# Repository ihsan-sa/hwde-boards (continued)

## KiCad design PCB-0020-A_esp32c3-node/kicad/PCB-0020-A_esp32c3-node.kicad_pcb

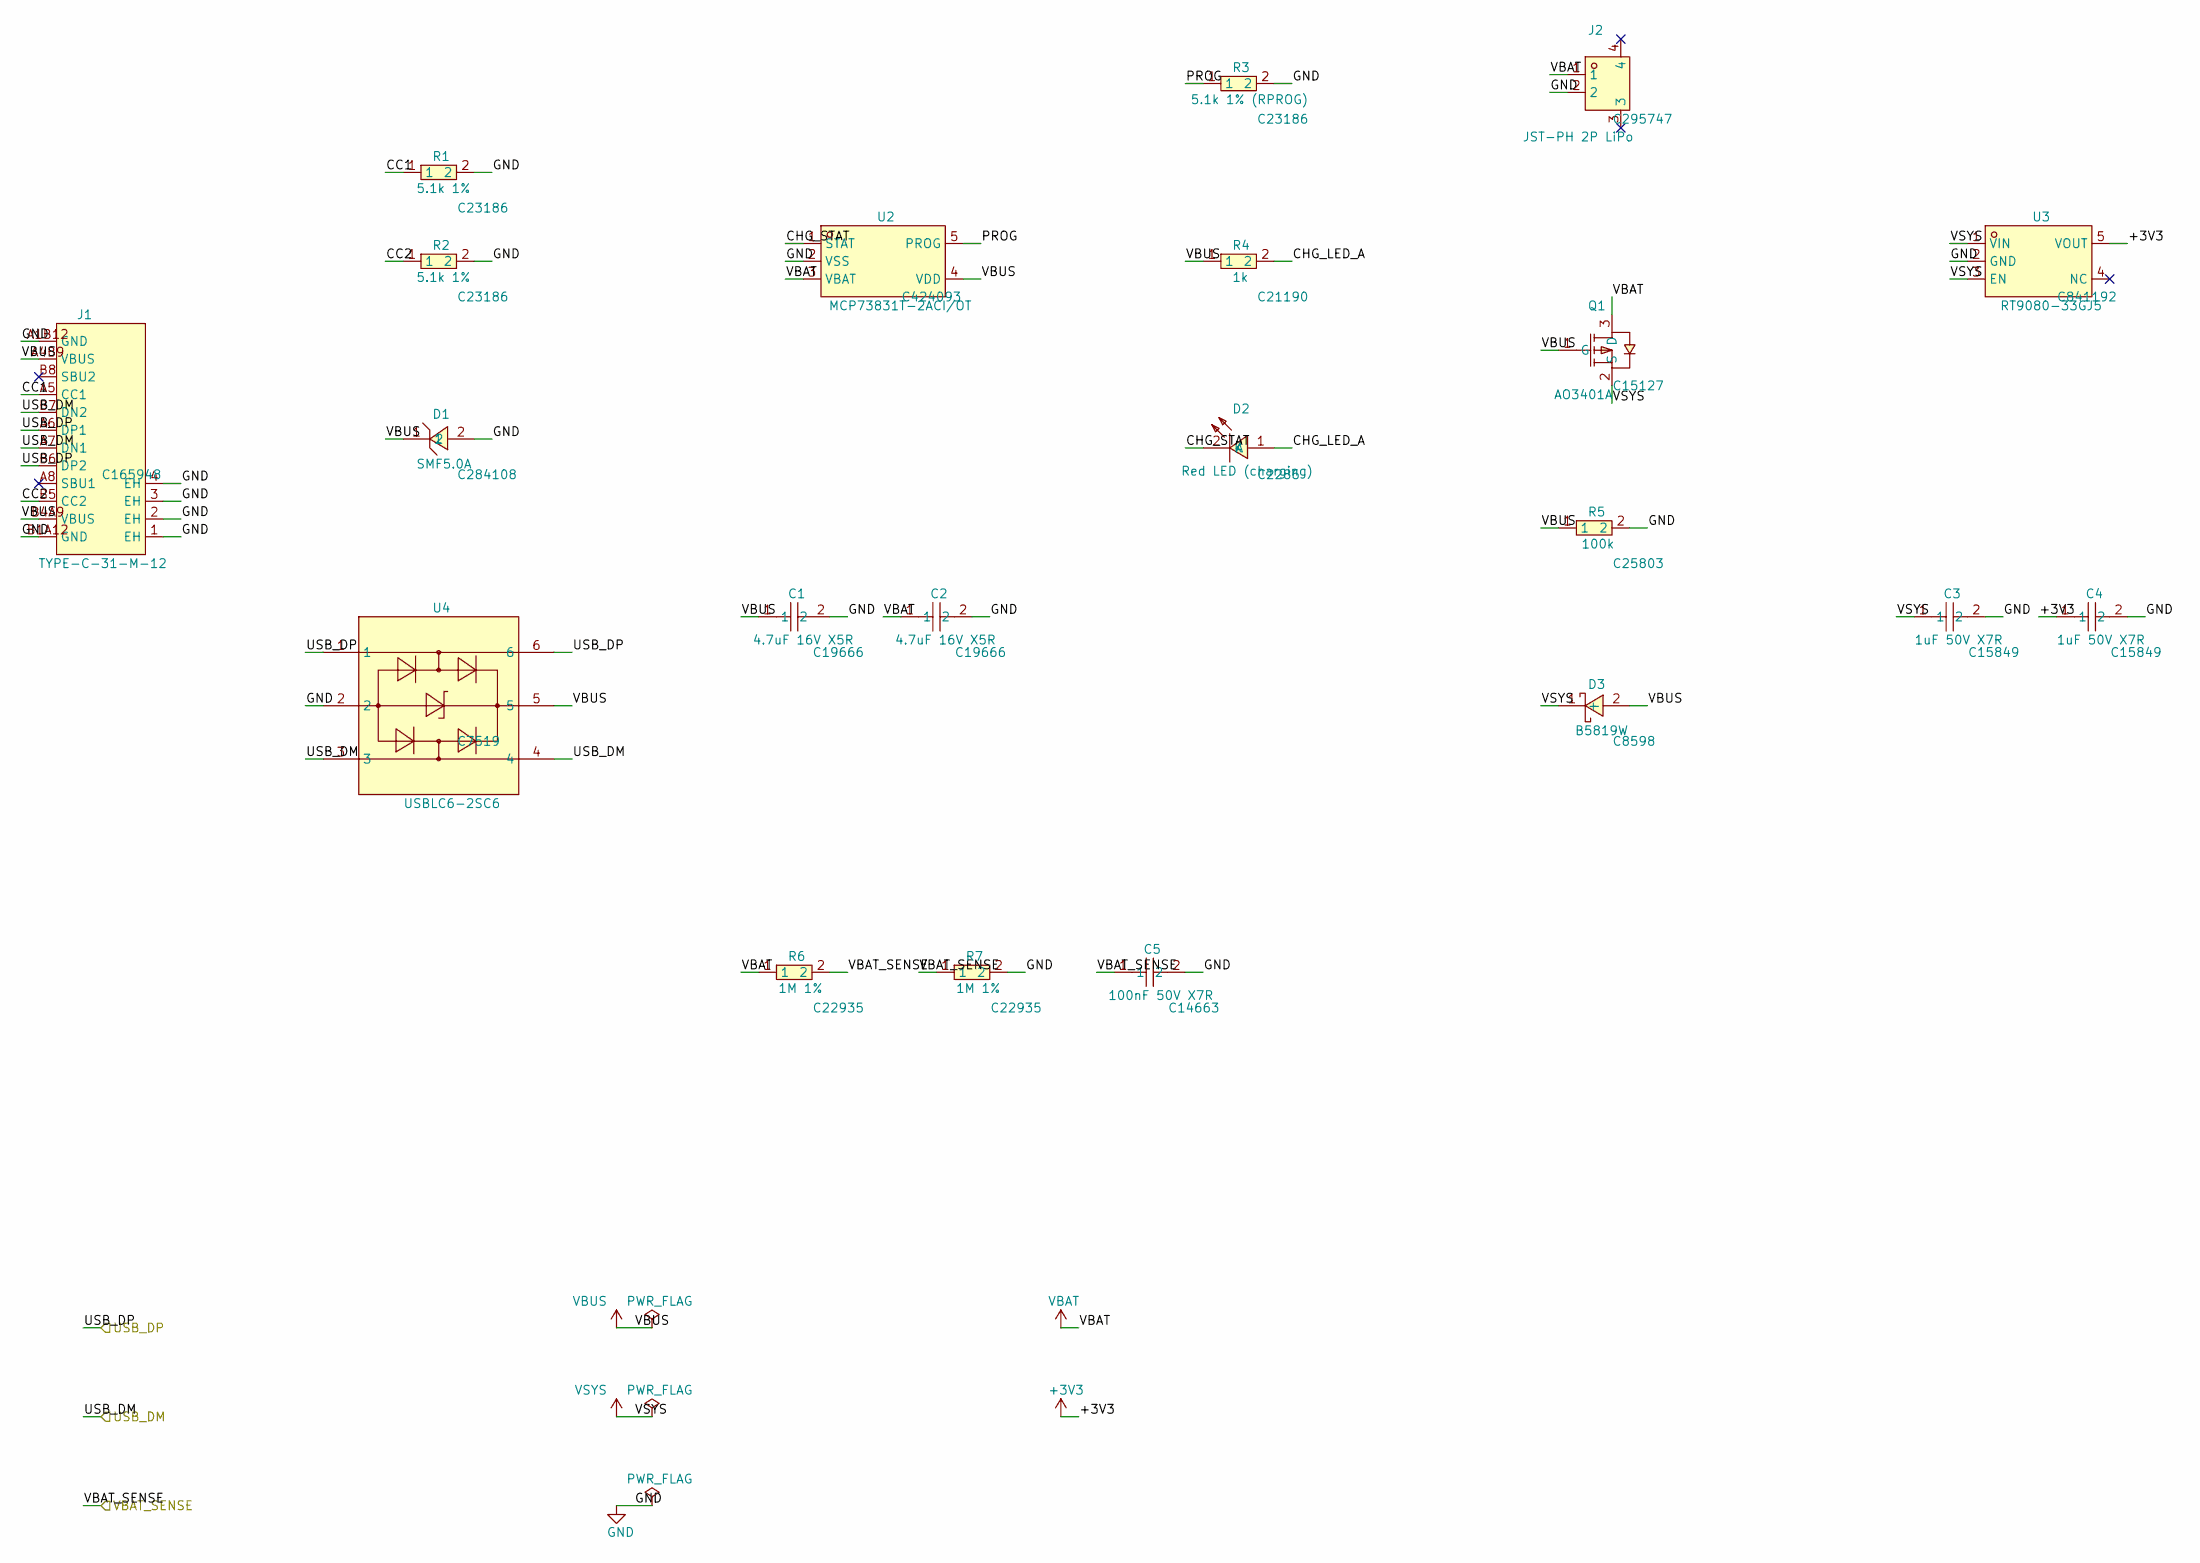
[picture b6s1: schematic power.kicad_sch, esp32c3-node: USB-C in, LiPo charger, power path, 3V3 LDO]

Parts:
C1, C2: 4.7uF 16V X5R; C0603; LCSC C19666
C3, C4: 1uF 50V X7R; C0603; LCSC C15849
C5: 100nF 50V X7R; C0603; LCSC C14663
D1: SMF5.0A; SOD-123_L2.8-W1.8-LS3.7-RD; LCSC C284108
D2: Red LED (charging); LED-SMD_L1.6-W0.8-R-RD; LCSC C2286
D3: B5819W; SOD-123_L2.7-W1.6-LS3.7-RD-1; LCSC C8598
J1: TYPE-C-31-M-12; USB-C_SMD-TYPE-C-31-M-12_1; LCSC C165948
J2: JST-PH 2P LiPo; CONN-SMD_P2.00_S2B-PH-SM4-TB-LF-SN; LCSC C295747
Q1: AO3401A; SOT-23_L2.9-W1.3-P1.90-LS2.4-BR; LCSC C15127
R1, R2: 5.1k 1%; R0603; LCSC C23186
R3: 5.1k 1% (RPROG); R0603; LCSC C23186
R4: 1k; R0603; LCSC C21190
R5: 100k; R0603; LCSC C25803
R6, R7: 1M 1%; R0603; LCSC C22935
U2: MCP73831T-2ACI/OT; SOT-23-5_L3.0-W1.7-P0.95-LS2.8-BL; LCSC C424093
U3: RT9080-33GJ5; TSOT-23-5_L2.9-W1.6-P0.95-LS2.8-BL; LCSC C841192
U4: USBLC6-2SC6; SOT-23-6_L2.9-W1.6-P0.95-LS2.8-BL; LCSC C7519

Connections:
+3V3: C4.1, U3.5 (VOUT); also elsewhere on the board
/USB_DM: J1.A7 (DN1), J1.B7 (DN2), U4.3, U4.4; also elsewhere on the board
/USB_DP: J1.A6 (DP1), J1.B6 (DP2), U4.1, U4.6; also elsewhere on the board
/VBAT_SENSE: C5.1, R6.2, R7.1; also elsewhere on the board
/power/CC1: J1.A5 (CC1), R1.1
/power/CC2: J1.B5 (CC2), R2.1
/power/CHG_LED_A: D2.1 (A), R4.2
/power/CHG_STAT: D2.2 (K), U2.1 (STAT)
/power/PROG: R3.1, U2.5 (PROG)
GND: C1.2, C2.2, C3.2, C4.2, C5.2, D1.2, J1.1 (EH), J1.2 (EH), J1.3 (EH), J1.4 (EH), J1.A1B12 (GND), J1.B1A12 (GND), J2.2, R1.2, R2.2, R3.2, R5.2, R7.2, U2.2 (VSS), U3.2 (GND), U4.2; also elsewhere on the board
VBAT: C2.1, J2.1, Q1.3 (D), R6.1, U2.3 (VBAT); also elsewhere on the board
VBUS: C1.1, D1.1, D3.2 (+), J1.A4B9 (VBUS), J1.B4A9 (VBUS), Q1.1 (G), R4.1, R5.1, U2.4 (VDD), U4.5; also elsewhere on the board
VSYS: C3.1, D3.1 (-), Q1.2 (S), U3.1 (VIN), U3.3 (EN)

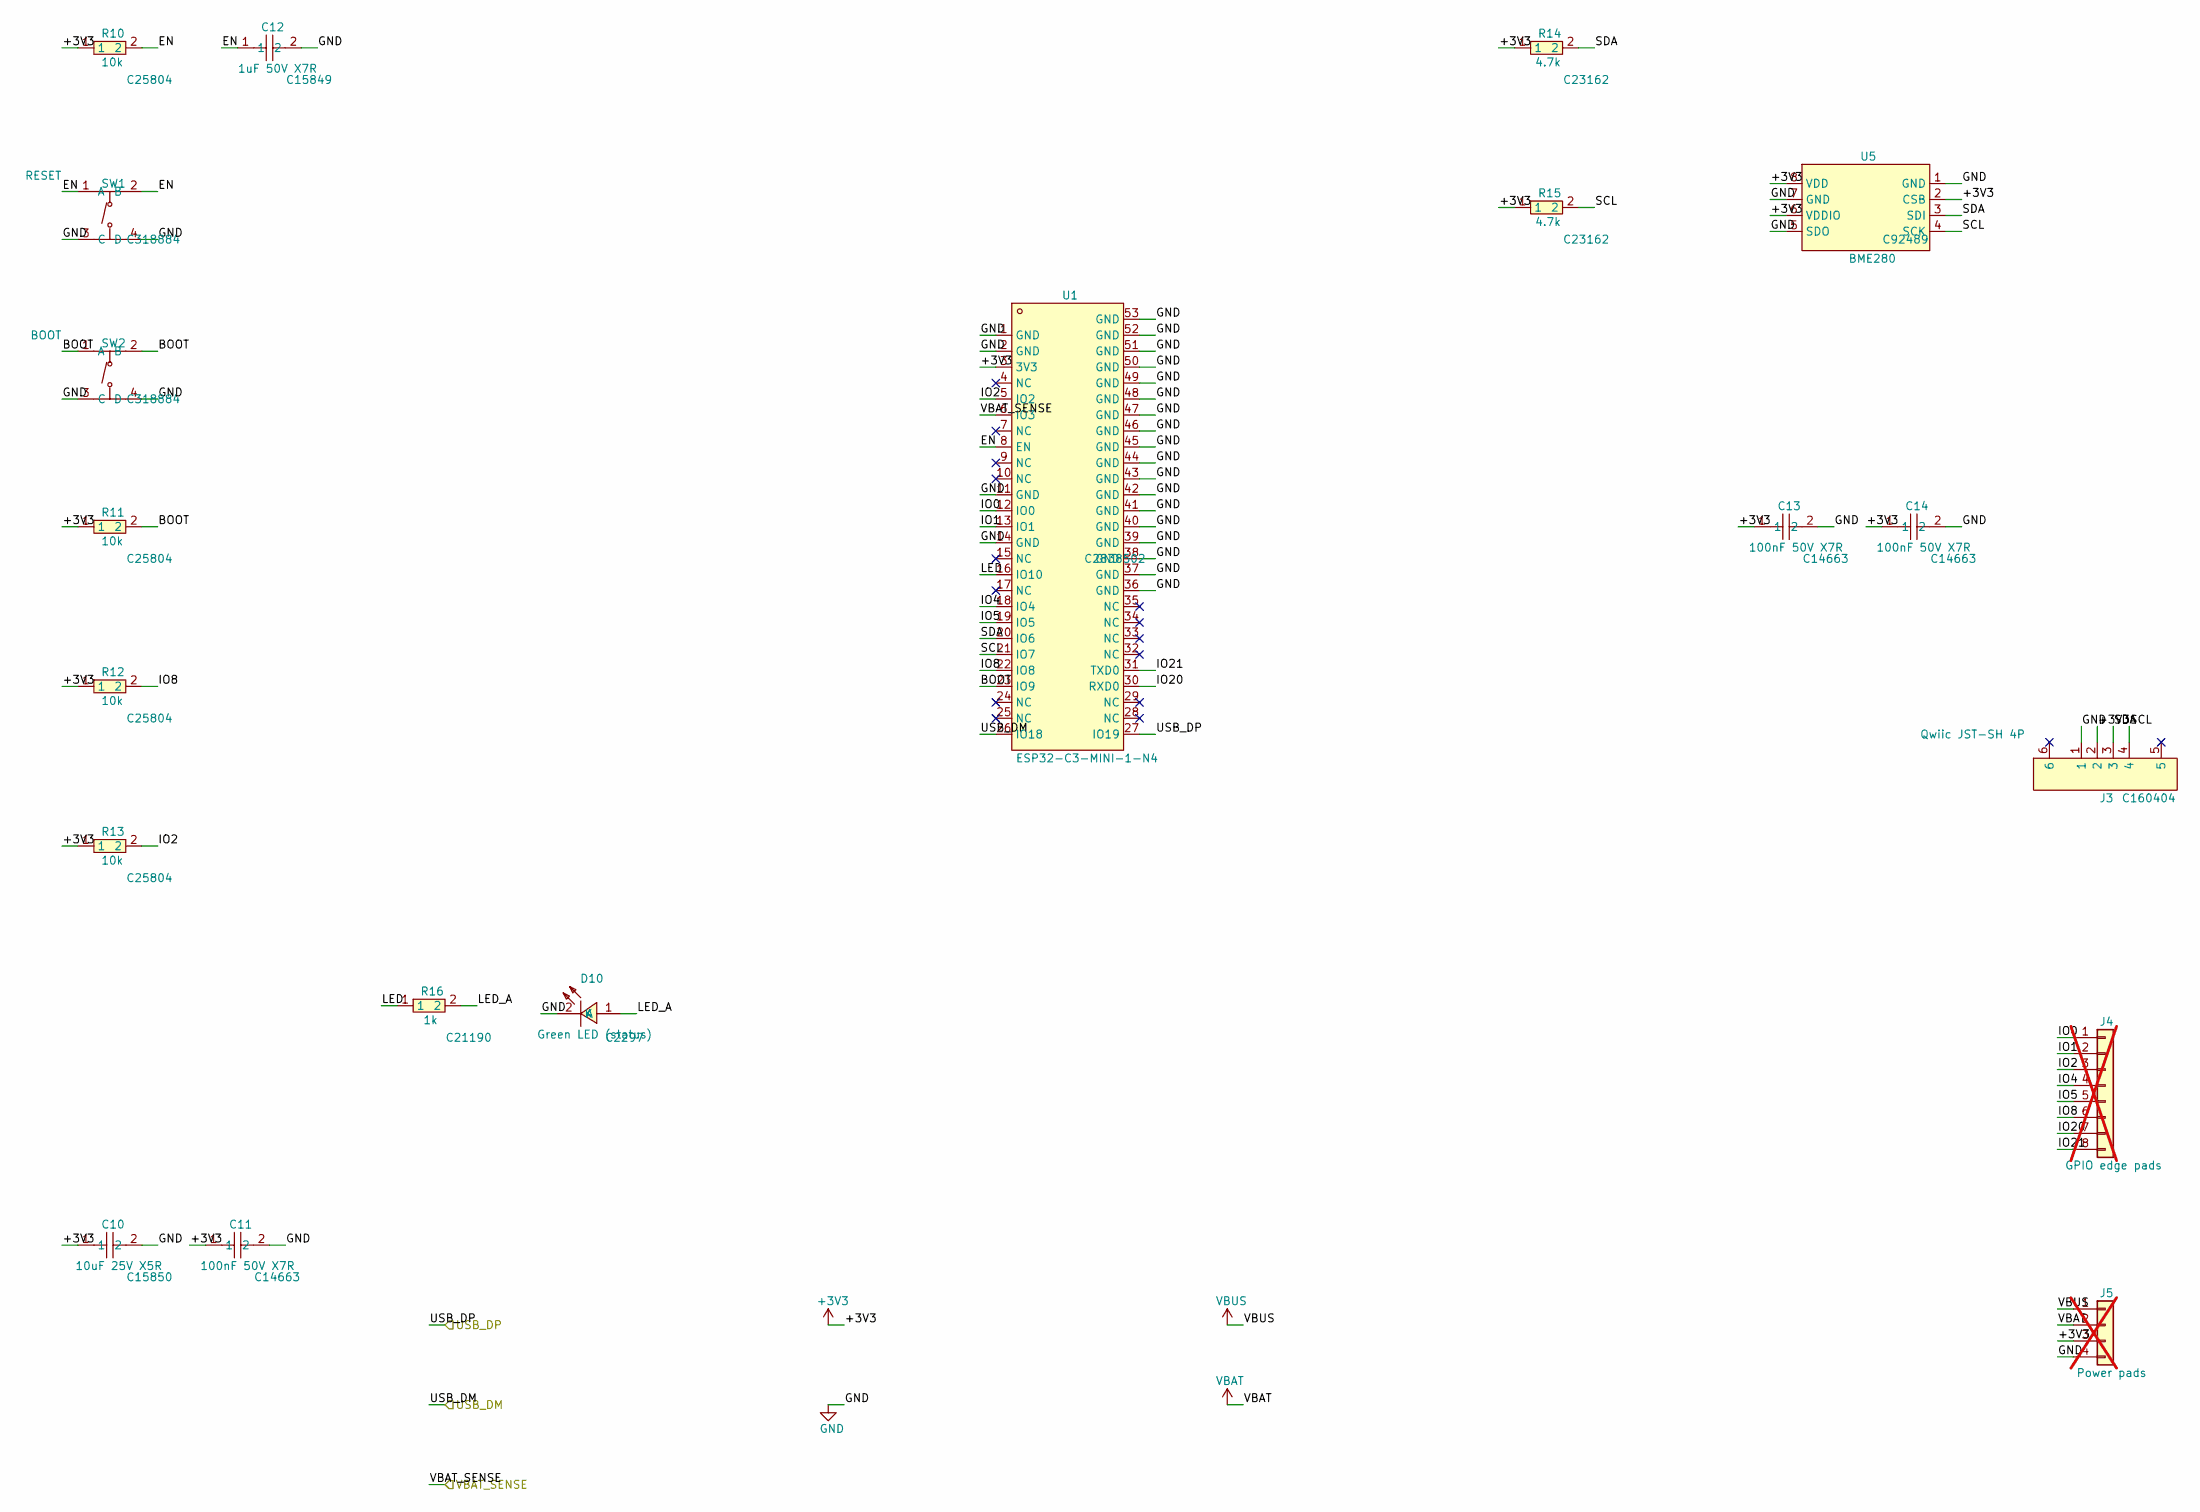
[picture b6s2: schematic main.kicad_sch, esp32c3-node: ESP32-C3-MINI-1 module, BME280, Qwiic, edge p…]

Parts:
C10: 10uF 25V X5R; C0805; LCSC C15850
C11, C13, C14: 100nF 50V X7R; C0603; LCSC C14663
C12: 1uF 50V X7R; C0603; LCSC C15849
D10: Green LED (status); LED0805-R-RD; LCSC C2297
J3: Qwiic JST-SH 4P; CONN-SMD_4P-P1.00_SM04B-SRSS-TB-LF-SN; LCSC C160404
J4: GPIO edge pads; PinHeader_1x08_P2.54mm_Vertical; not fitted
J5: Power pads; PinHeader_1x04_P2.54mm_Vertical; not fitted
R10, R11, R12, R13: 10k; R0603; LCSC C25804
R14, R15: 4.7k; R0603; LCSC C23162
R16: 1k; R0603; LCSC C21190
SW1: RESET; SW-SMD_4P-L5.1-W5.1-P3.70-LS6.5-TL_H1.5; LCSC C318884
SW2: BOOT; SW-SMD_4P-L5.1-W5.1-P3.70-LS6.5-TL_H1.5; LCSC C318884
U1: ESP32-C3-MINI-1-N4; WIFIM-SMD_ESP32-C3-MINI-1; LCSC C2838502
U5: BME280; LGA-8_BME280_BL; LCSC C92489

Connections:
+3V3: C10.1, C11.1, C13.1, C14.1, J3.2, J5.3, R10.1, R11.1, R12.1, R13.1, R14.1, R15.1, U1.3 (3V3), U5.2 (CSB), U5.6 (VDDIO), U5.8 (VDD); also elsewhere on the board
/USB_DM: U1.26 (IO18); also elsewhere on the board
/USB_DP: U1.27 (IO19); also elsewhere on the board
/VBAT_SENSE: U1.6 (IO3); also elsewhere on the board
/main/BOOT: R11.2, SW2.1 (A), SW2.2 (B), U1.23 (IO9)
/main/EN: C12.1, R10.2, SW1.1 (A), SW1.2 (B), U1.8 (EN)
/main/IO0: J4.1, U1.12 (IO0)
/main/IO1: J4.2, U1.13 (IO1)
/main/IO2: J4.3, R13.2, U1.5 (IO2)
/main/IO4: J4.4, U1.18 (IO4)
/main/IO5: J4.5, U1.19 (IO5)
/main/IO8: J4.6, R12.2, U1.22 (IO8)
/main/IO20: J4.7, U1.30 (RXD0)
/main/IO21: J4.8, U1.31 (TXD0)
/main/LED: R16.1, U1.16 (IO10)
/main/LED_A: D10.1 (A), R16.2
/main/SCL: J3.4, R15.2, U1.21 (IO7), U5.4 (SCK)
/main/SDA: J3.3, R14.2, U1.20 (IO6), U5.3 (SDI)
GND: C10.2, C11.2, C12.2, C13.2, C14.2, D10.2 (K), J3.1, J5.4, SW1.3 (C), SW1.4 (D), SW2.3 (C), SW2.4 (D), U1.1 (GND), U1.2 (GND), U1.11 (GND), U1.14 (GND), U1.36 (GND), U1.37 (GND), U1.38 (GND), U1.39 (GND), U1.40 (GND), U1.41 (GND), U1.42 (GND), U1.43 (GND), U1.44 (GND), U1.45 (GND), U1.46 (GND), U1.47 (GND), U1.48 (GND), U1.49 (GND), U1.50 (GND), U1.51 (GND), U1.52 (GND), U1.53 (GND), U5.1 (GND), U5.5 (SDO), U5.7 (GND); also elsewhere on the board
VBAT: J5.2; also elsewhere on the board
VBUS: J5.1; also elsewhere on the board

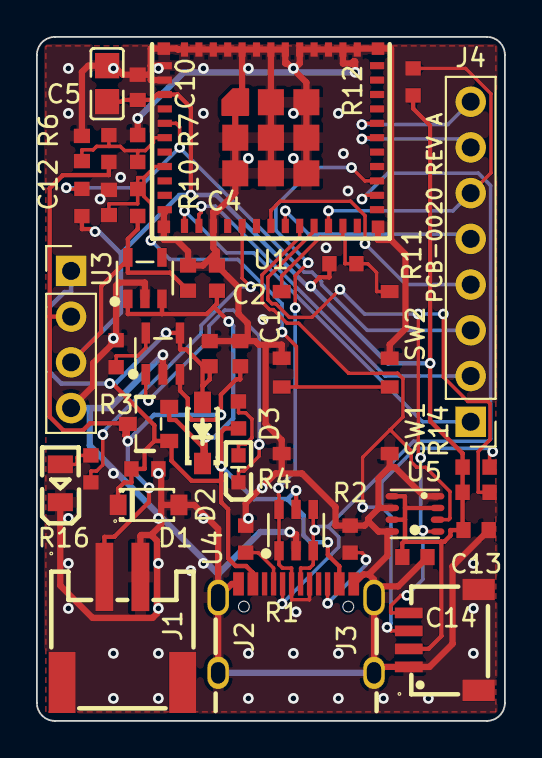
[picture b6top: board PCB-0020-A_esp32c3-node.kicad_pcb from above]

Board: 2 copper layers, 26.0 x 38.0 mm, 41 parts (0 on the bottom side), 27 nets.

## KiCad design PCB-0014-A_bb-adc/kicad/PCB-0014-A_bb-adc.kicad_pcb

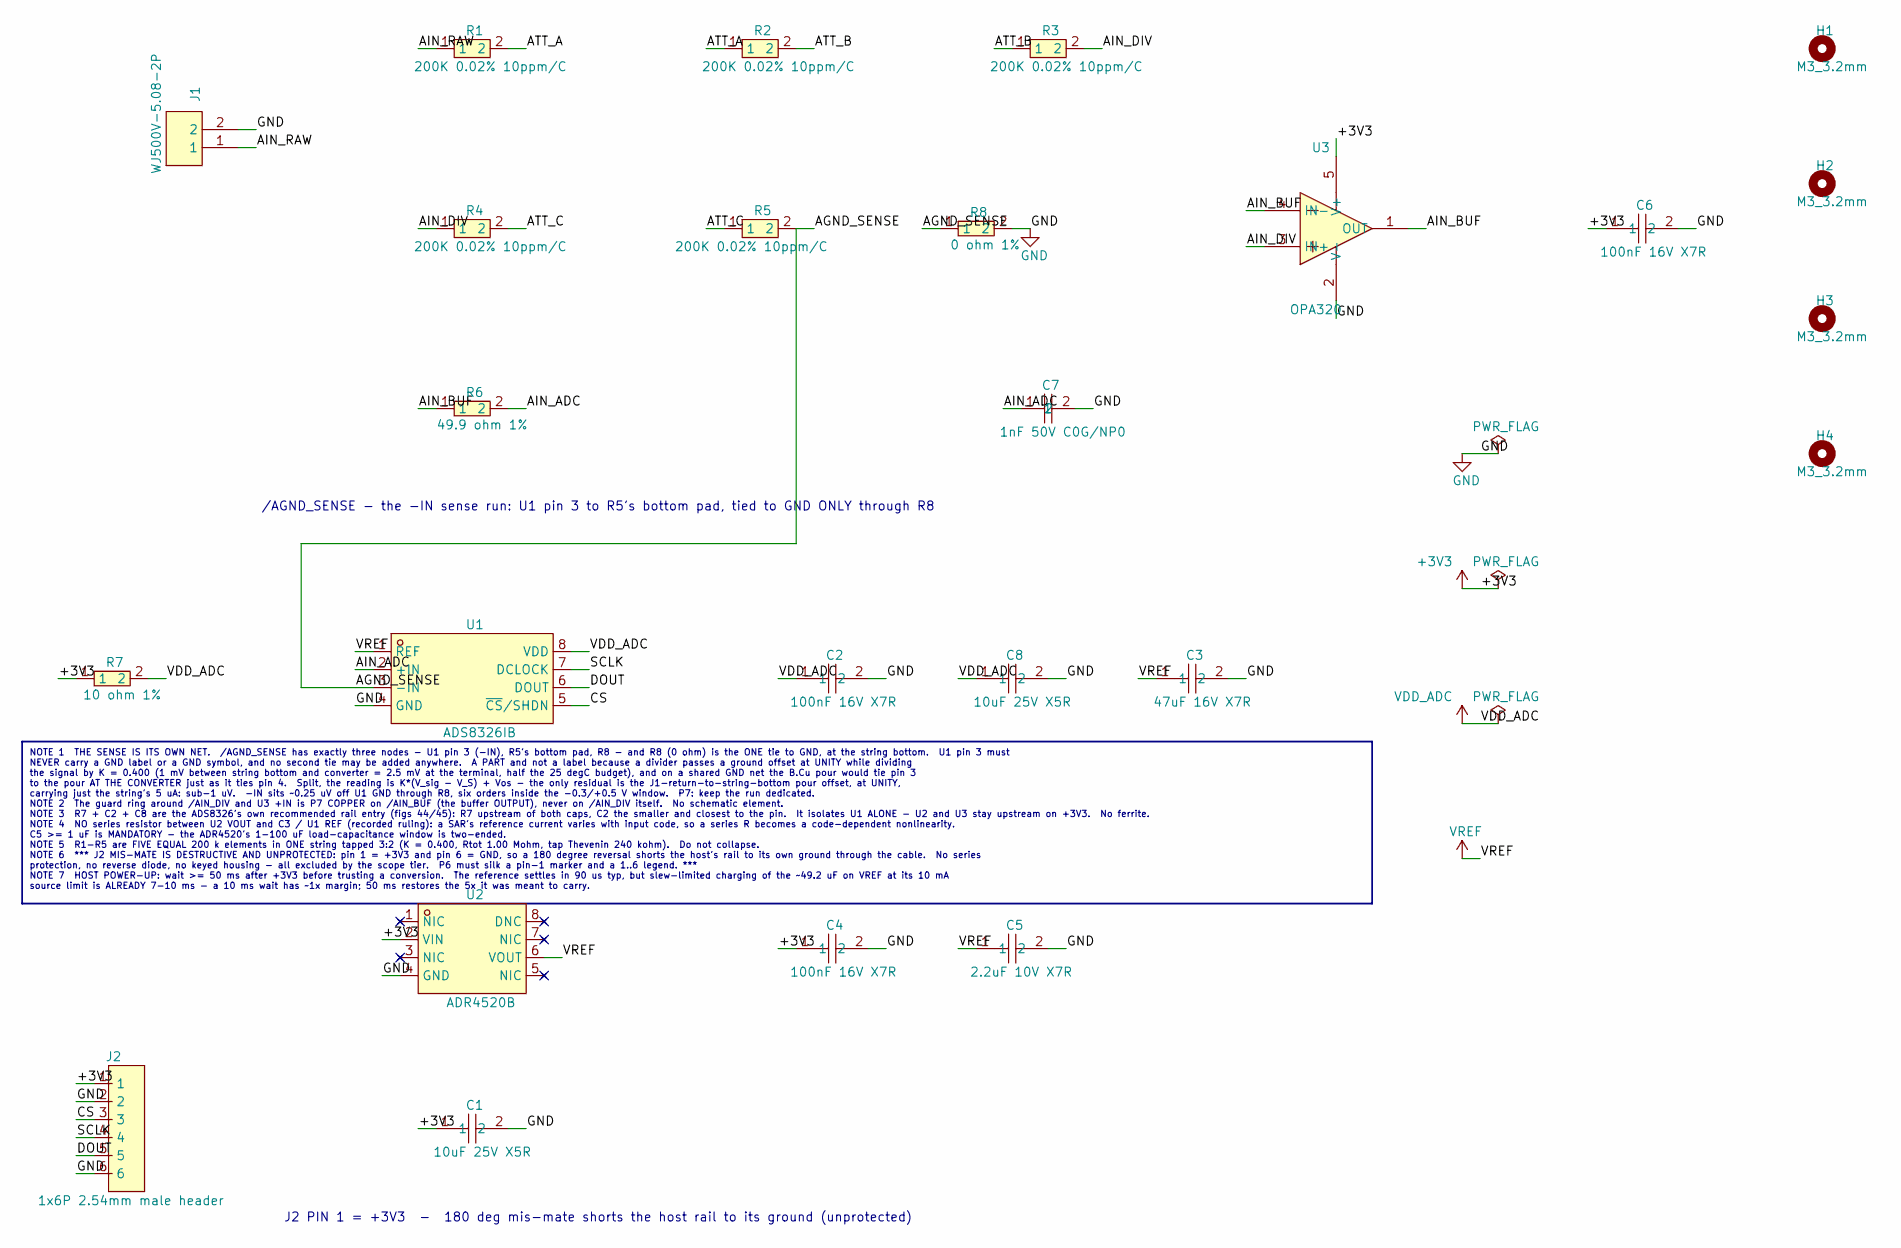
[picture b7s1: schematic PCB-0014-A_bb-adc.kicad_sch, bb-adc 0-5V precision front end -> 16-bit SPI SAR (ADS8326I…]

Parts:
C1, C8: 10uF 25V X5R; C0805; LCSC C15850
C2, C4, C6: 100nF 16V X7R; C0402; LCSC C1525
C3: 47uF 16V X7R; C1210; LCSC C5440143
C5: 2.2uF 10V X7R; C0603; LCSC C513691
C7: 1nF 50V C0G/NP0; C0603; LCSC C106246
H1, H2, H3, H4: M3_3.2mm; MountingHole_3.2mm_M3
J1: WJ500V-5.08-2P; CONN-TH_2P-P5.00_WJ500V-5.08-2P; LCSC C8465
J2: 1x6P 2.54mm male header; HDR-TH_6P-P2.54-V-M-1; LCSC C37208
R1, R2, R3, R4, R5: 200K 0.02% 10ppm/C; R0805; LCSC C23067436
R6: 49.9 ohm 1%; R0603; LCSC C23185
R7: 10 ohm 1%; R0603; LCSC C22859
R8: 0 ohm 1%; R0603; LCSC C21189
U1: ADS8326IB; VSSOP-8_L3.0-W3.0-P0.65-LS5.0-BL; LCSC C544731
U2: ADR4520B; SOIC-8_L5.0-W4.0-P1.27-LS6.0-BL; LCSC C579305
U3: OPA320; SOT-23-5_L3.0-W1.7-P0.95-LS2.8-BR; LCSC C92494

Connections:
+3V3: C1.1, C4.1, C6.1, J2.1, R7.1, U2.2 (VIN), U3.5 (V+)
/AGND_SENSE: R5.2, R8.1, U1.3 (-IN)
/AIN_ADC: C7.1, R6.2, U1.2 (+IN)
/AIN_BUF: R6.1, U3.1 (OUT), U3.4 (IN-)
/AIN_DIV: R3.2, R4.1, U3.3 (IN+)
/AIN_RAW: J1.1, R1.1
/ATT_A: R1.2, R2.1
/ATT_B: R2.2, R3.1
/ATT_C: R4.2, R5.1
/CS: J2.3, U1.5 (~CS/SHDN)
/DOUT: J2.5, U1.6 (DOUT)
/SCLK: J2.4, U1.7 (DCLOCK)
GND: C1.2, C2.2, C3.2, C4.2, C5.2, C6.2, C7.2, C8.2, J1.2, J2.2, J2.6, R8.2, U1.4 (GND), U2.4 (GND), U3.2 (V-)
VDD_ADC: C2.1, C8.1, R7.2, U1.8 (VDD)
VREF: C3.1, C5.1, U1.1 (REF), U2.6 (VOUT)

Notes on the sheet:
/AGND_SENSE - the -IN sense run: U1 pin 3 to R5's bottom pad, tied to GND ONLY through R8
J2 PIN 1 = +3V3 - 180 deg mis-mate shorts the host rail to its ground (unprotected)
NOTE 1 THE SENSE IS ITS OWN NET. /AGND_SENSE has exactly three nodes - U1 pin 3 (-IN), R5's bottom pad, R8 - and R8 (0 ohm) is the ONE tie to GND, at the string bottom. U1 pin 3 must NEVER carry a GND label or a GND symbol, and no second tie may be added anywhere. A PART and not a label because a d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

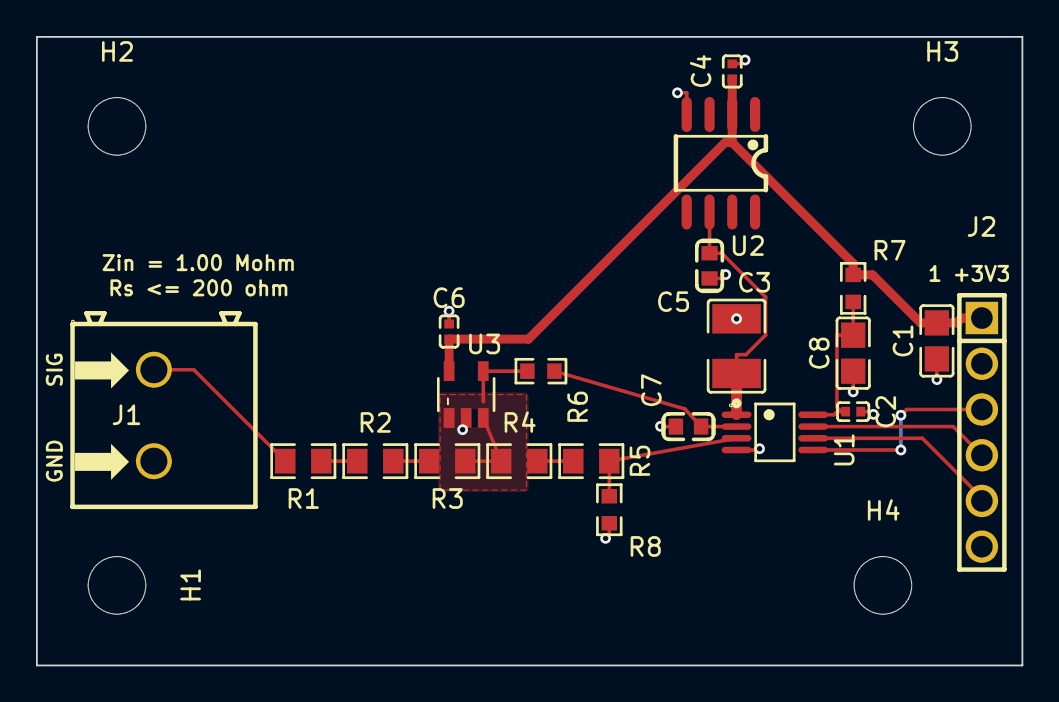
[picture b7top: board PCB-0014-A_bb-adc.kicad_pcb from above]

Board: 2 copper layers, 54.8 x 34.9 mm, 25 parts (0 on the bottom side), 15 nets.

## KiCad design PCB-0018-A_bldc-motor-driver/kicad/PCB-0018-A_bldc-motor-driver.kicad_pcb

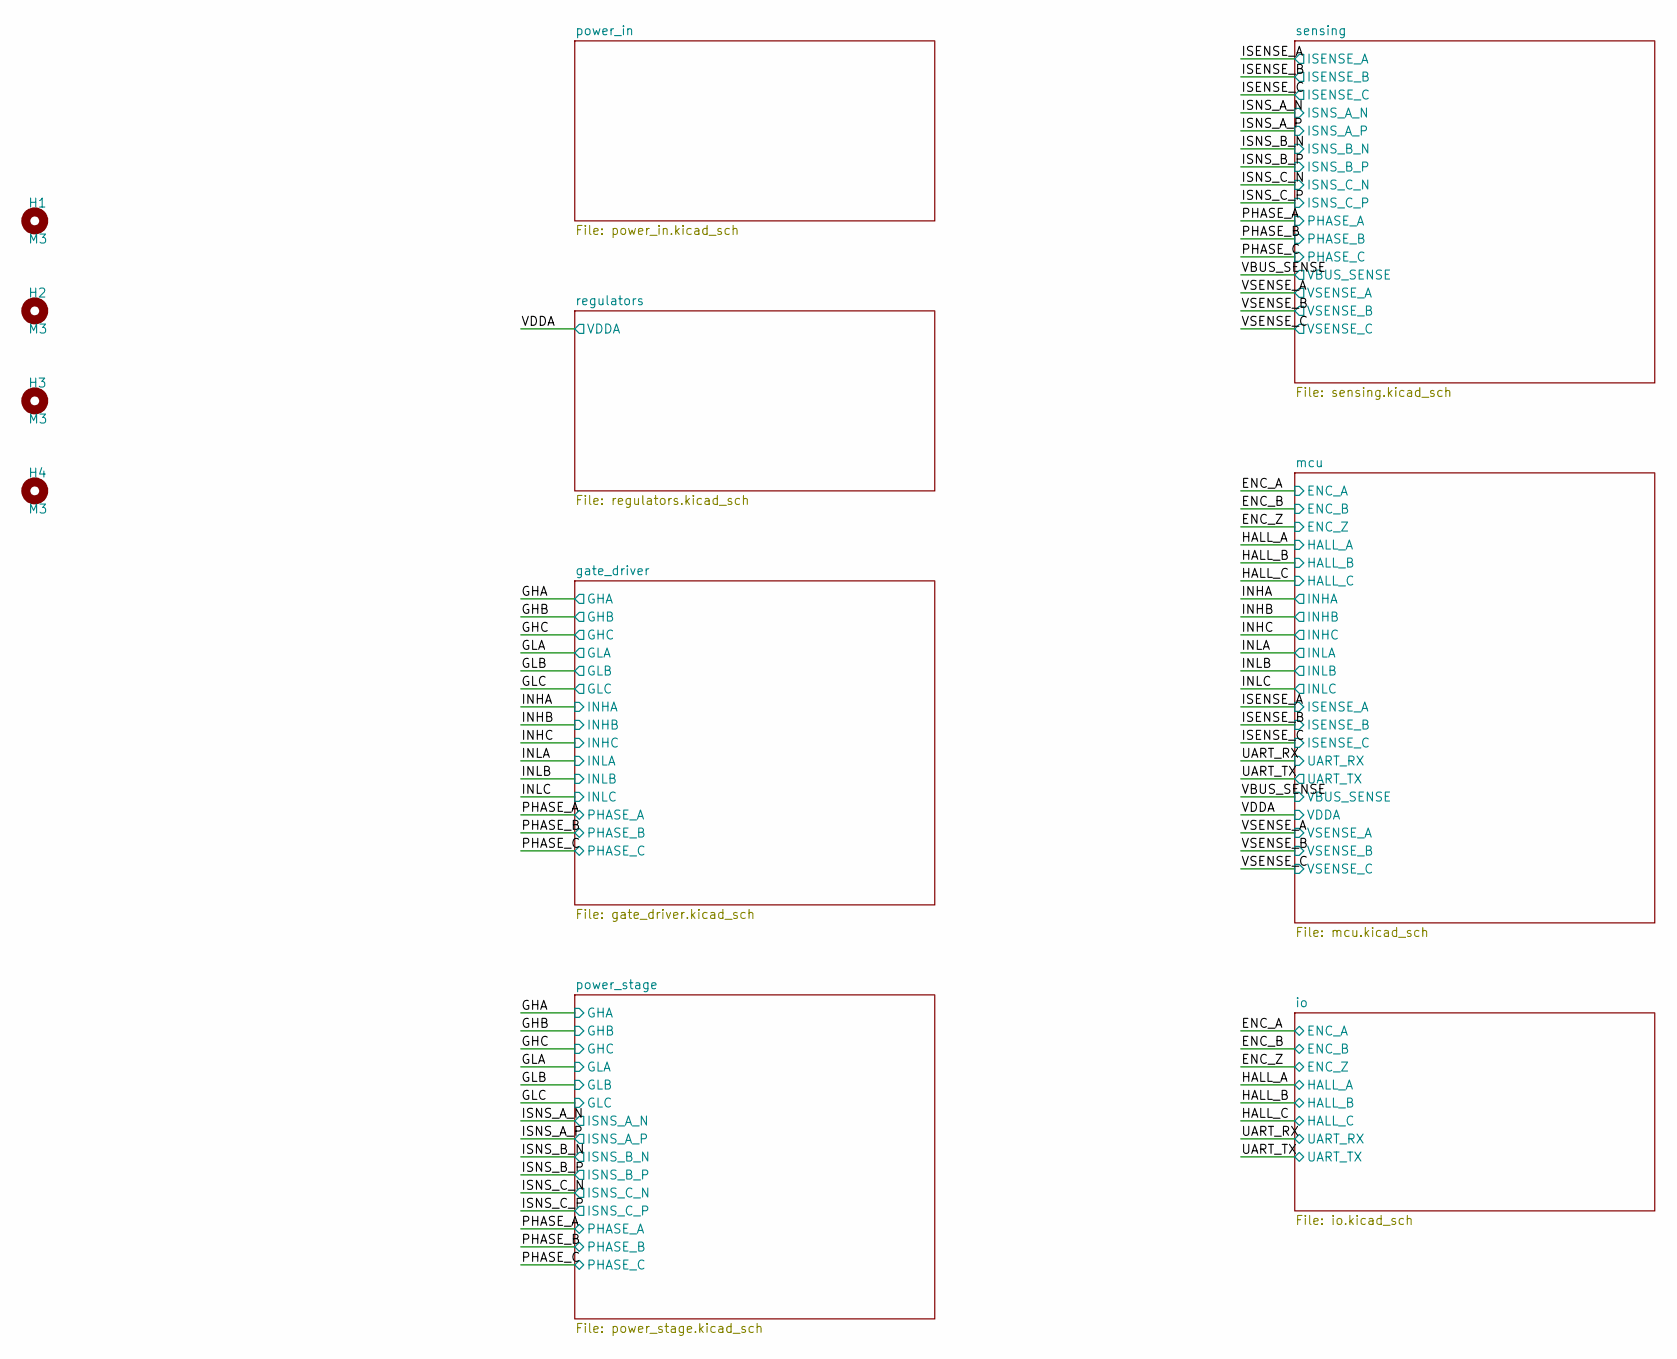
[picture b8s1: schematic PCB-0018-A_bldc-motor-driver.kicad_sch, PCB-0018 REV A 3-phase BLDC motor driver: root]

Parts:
H1, H2, H3, H4: M3; MountingHole_3.2mm_M3

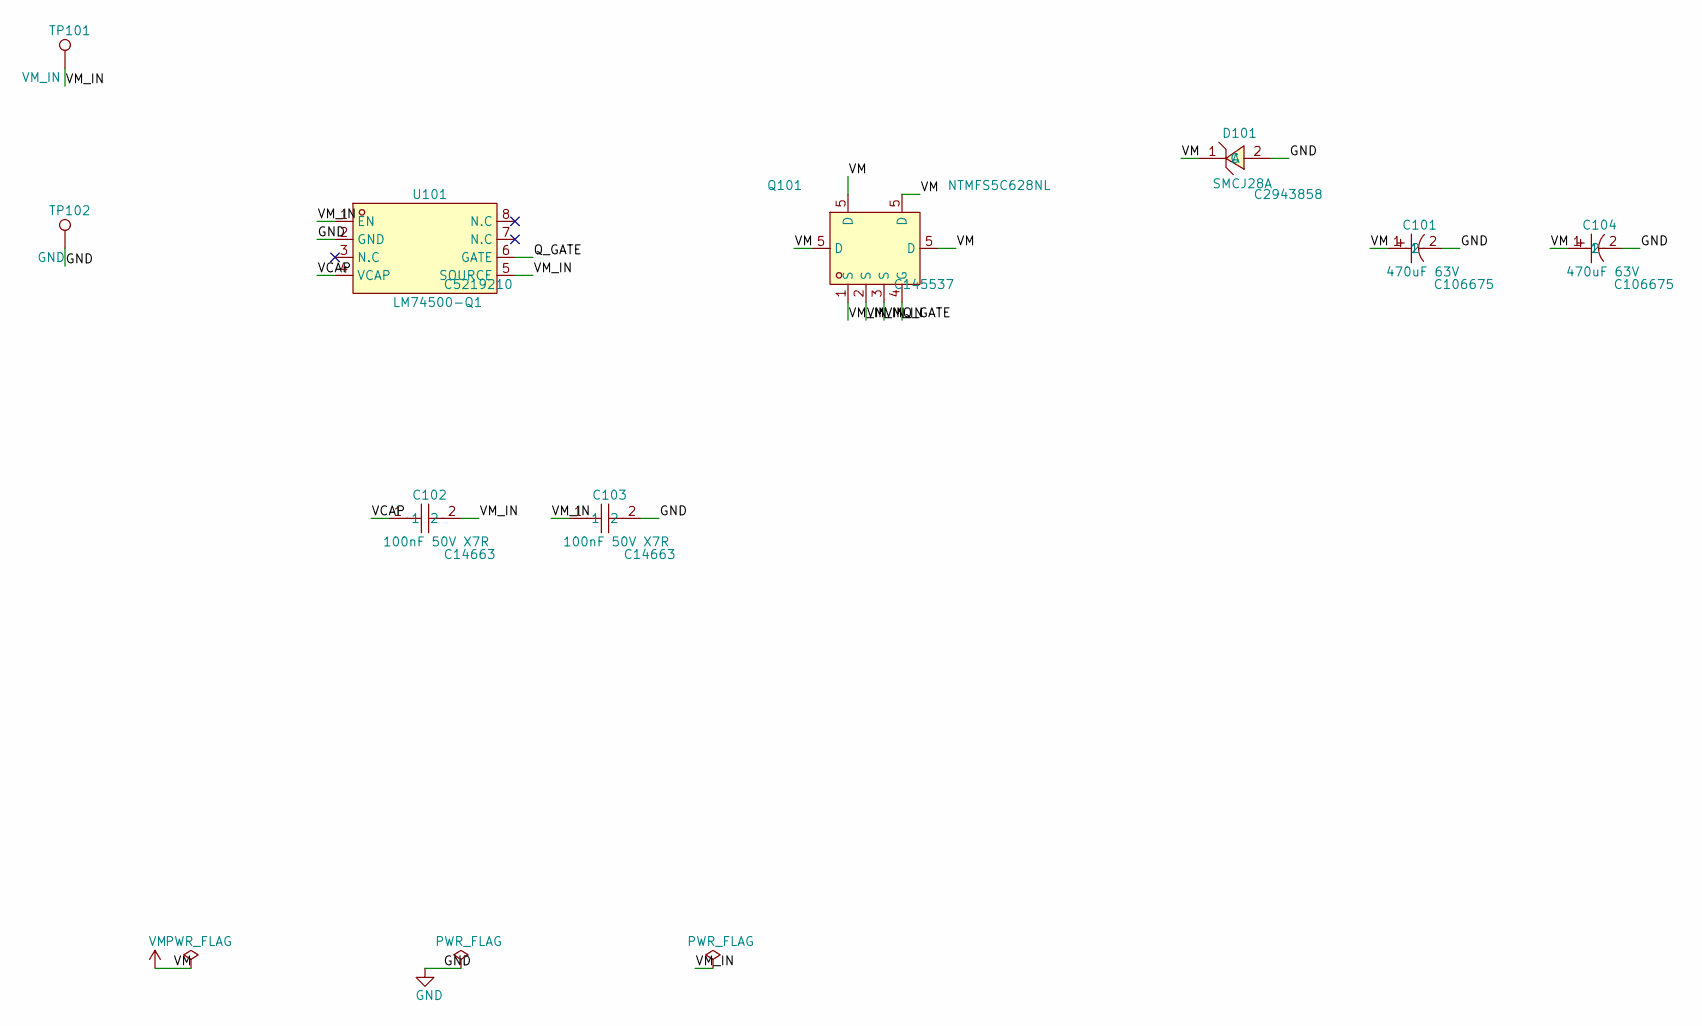
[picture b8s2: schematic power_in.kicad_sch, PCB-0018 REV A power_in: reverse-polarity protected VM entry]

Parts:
C101, C104: 470uF 63V; CAP-TH_BD13.0-P5.00-D1.2-FD; LCSC C106675
C102, C103: 100nF 50V X7R; C0603; LCSC C14663
D101: SMCJ28A; SMC_L6.9-W5.8-LS7.9-RD; LCSC C2943858
Q101: NTMFS5C628NL; DFN-5_L4.9-W5.9-P1.27-LS6.2-BL; LCSC C145537
TP101: VM_IN; TestPoint_THTPad_4.0x4.0mm_Drill2.0mm
TP102: GND; TestPoint_THTPad_4.0x4.0mm_Drill2.0mm
U101: LM74500-Q1; SOT-23-8_L3.0-W1.7-P0.65-LS2.8-BR; LCSC C5219210

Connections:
/power_in/Q_GATE: Q101.4 (G), U101.6 (GATE)
/power_in/VCAP: C102.1, U101.4 (VCAP)
/power_in/VM_IN: C102.2, C103.1, Q101.1 (S), Q101.2 (S), Q101.3 (S), TP101.1, U101.1 (EN), U101.5 (SOURCE)
GND: C101.2, C103.2, C104.2, D101.2 (A), TP102.1, U101.2 (GND); also elsewhere on the board
VM: C101.1, C104.1, D101.1 (C), Q101.5 (D); also elsewhere on the board
